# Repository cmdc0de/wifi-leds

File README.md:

# wifi-leds
wifi controlled LEDs

Goal of project:
* Build a web server on esp 32
* use a n-type mosfet to control power to an APA 102c LED strip
* use a ATECC608a for crypto and random number generator. you ask why? I say why not?
* add 2 displays 1. 2.4 SPI touch screen and 1 OLED I2C 
  * Again you ask why? mostly becuase I'm also working on the darknet 8 badge and one of these will be on that badge and it'll help me prepare.
* Pull out JTAG pins so I can try to debug from container.  Harder than it sounds becuase you need to run the open ocd server

Secondary Goals:
* Make the traces as thick as possible, so I can try to not only mill the board with my Bantam but also use 'print' the board using the Voltera.

Code:
* On linux:
* run buildESPContainer.sh
* ./runESPContainer.sh
* cd into firmware directory
* make menuconfig - set up usb port your usb to serial programmer is registered as
* make flash - build and push to dev board
* make monitor 
*

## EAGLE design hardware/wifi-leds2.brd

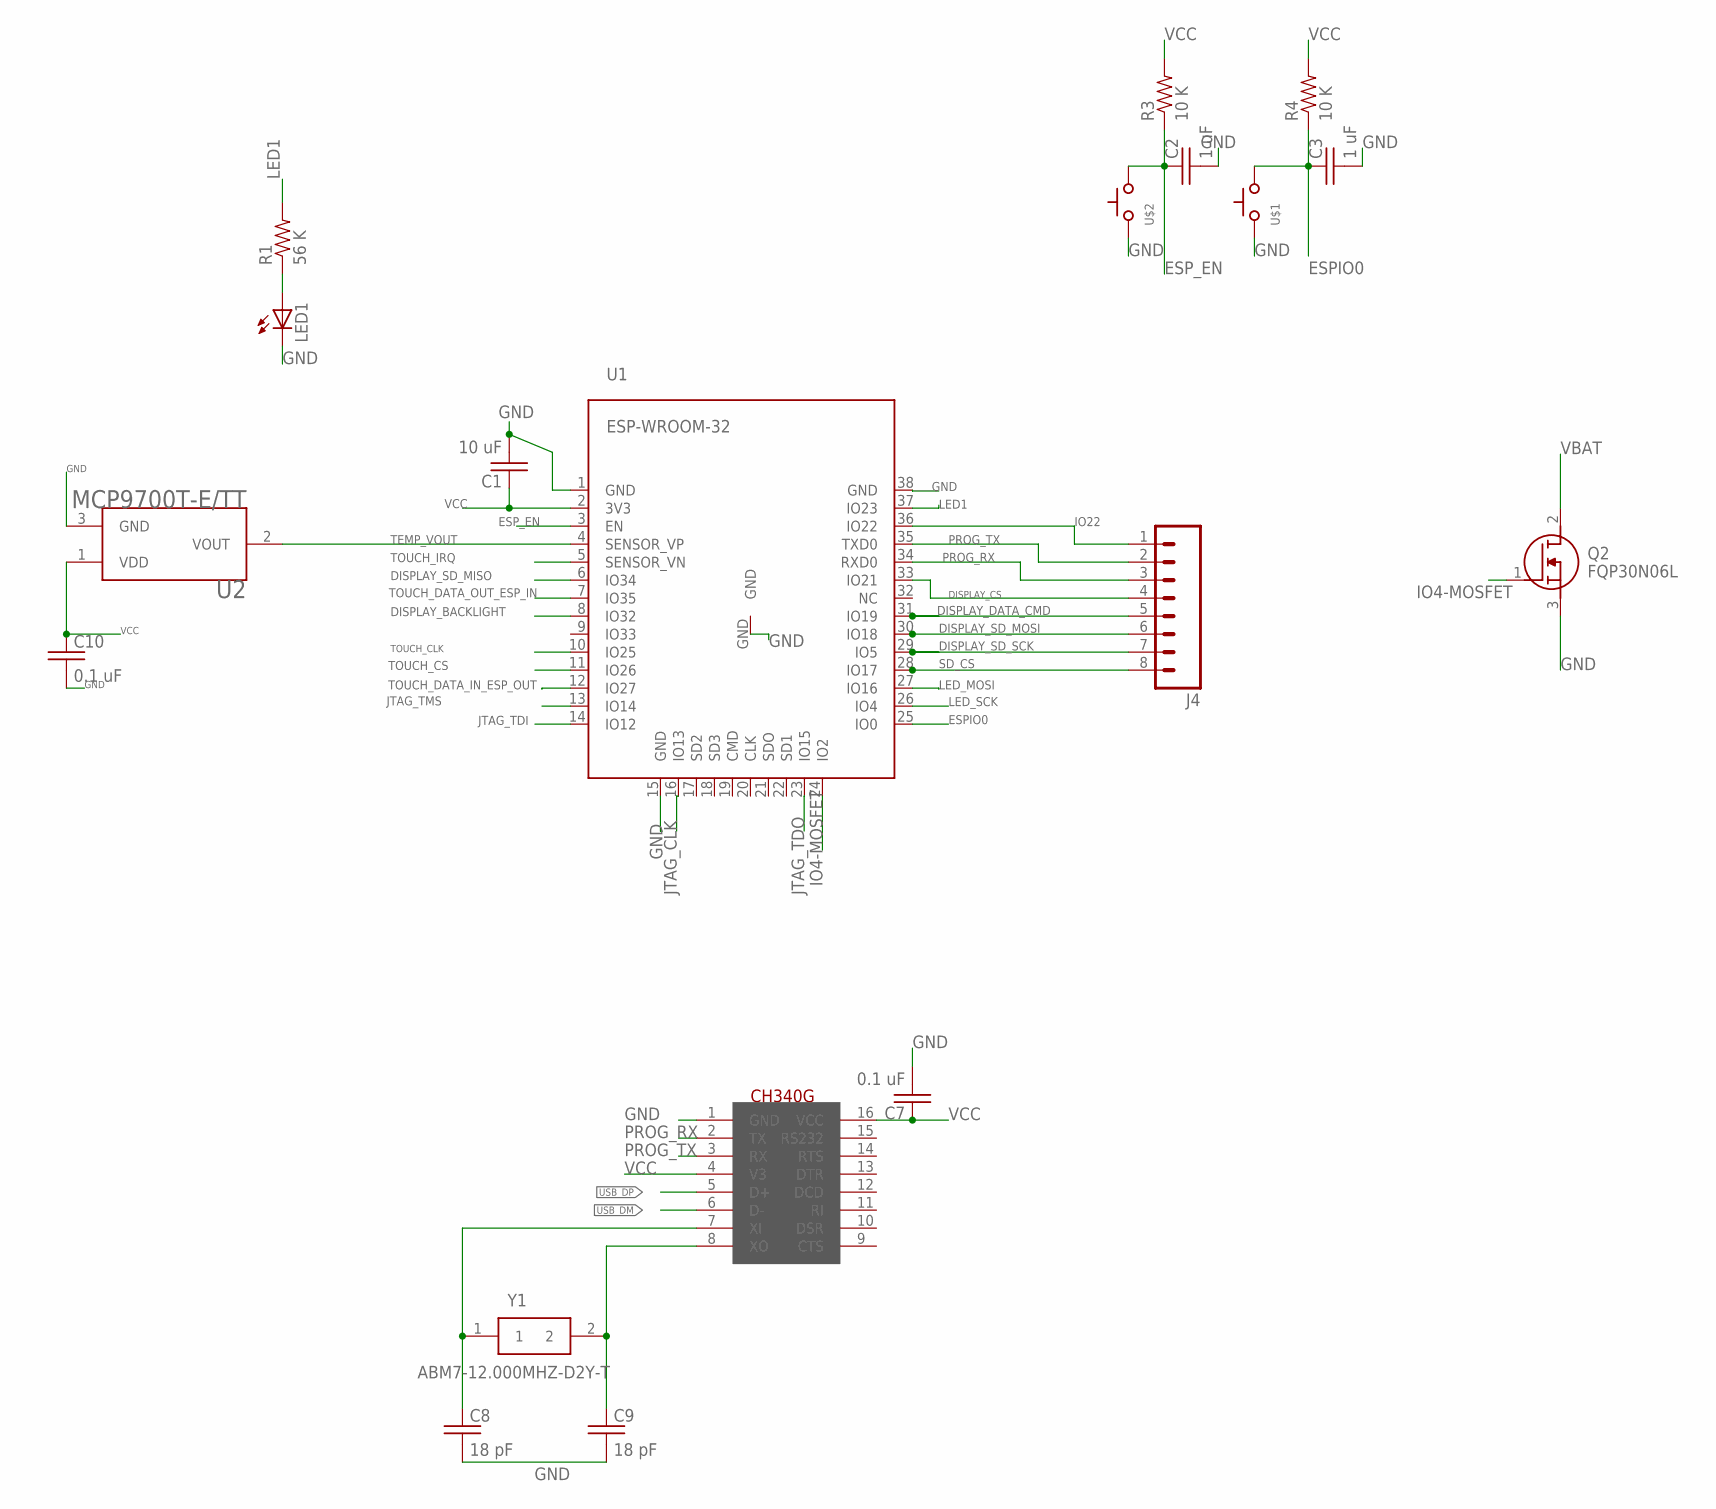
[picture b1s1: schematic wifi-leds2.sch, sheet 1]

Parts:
C1: 10 uF; C0805
C2, C3: 1 uF; C0805
C7, C10: 0.1 uF; C0805
C8, C9: 18 pF; C0805
J4: M08; 1X08_ROUND
LED1: LED3MM
Q2: FQP30N06L; TO254P470X1016X2019-3P
R1: 56 K; 0805
R3, R4: 10 K; 0805
U1: ESP-WROOM-32
U2: MCP9700T-E/TT; SOT95P237X112-3N
U$1, U$2: SWITCH_TACTILETACTILE-2PIN-NARROW; TACTILE-2PIN-NARROW
U$6: CH340G; SOIC16
Y1: ABM7-12.000MHZ-D2Y-T; ABM7

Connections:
DISPLAY_BACKLIGHT: U1.8 (IO32); also elsewhere on the board
DISPLAY_CS: J4.4, U1.33 (IO21); also elsewhere on the board
DISPLAY_DATA_CMD: J4.5, U1.31 (IO19); also elsewhere on the board
DISPLAY_SD_MISO: U1.6 (IO34); also elsewhere on the board
DISPLAY_SD_MOSI: J4.6, U1.30 (IO18); also elsewhere on the board
DISPLAY_SD_SCK: J4.7, U1.29 (IO5); also elsewhere on the board
ESPIO0: C3.1, R4.1, U1.25 (IO0), U$1.P$1 (A)
ESP_EN: C2.1, R3.1, U1.3 (EN), U$2.P$1 (A)
GND: C1.2, C2.2, C3.2, C7.2, C8.2, C9.2, C10.2, LED1.K (C), Q2.3 (S), U1.1 (GND), U1.15 (GND), U1.38 (GND), U1.GND, U2.3 (GND), U$1.P$2 (C), U$2.P$2 (C), U$6.1 (GND); also elsewhere on the board
IO4-MOSFET: Q2.1 (G), U1.24 (IO2)
IO22: J4.1, U1.36 (IO22)
JTAG_CLK: U1.16 (IO13); also elsewhere on the board
JTAG_TDI: U1.14 (IO12); also elsewhere on the board
JTAG_TDO: U1.23 (IO15); also elsewhere on the board
JTAG_TMS: U1.13 (IO14); also elsewhere on the board
LED1: R1.2, U1.37 (IO23)
LED_MOSI: U1.27 (IO16); also elsewhere on the board
LED_SCK: U1.26 (IO4); also elsewhere on the board
unnamed: LED1.A, R1.1
unnamed: C8.1, U$6.7 (XI), Y1.1
unnamed: C9.1, U$6.8 (XO), Y1.2
PROG_RX: J4.3, U1.34 (RXD0), U$6.2 (TX); also elsewhere on the board
PROG_TX: J4.2, U1.35 (TXD0), U$6.3 (RX); also elsewhere on the board
SD_CS: J4.8, U1.28 (IO17); also elsewhere on the board
TEMP_VOUT: U1.4 (SENSOR_VP), U2.2 (VOUT)
TOUCH_CLK: U1.10 (IO25); also elsewhere on the board
TOUCH_CS: U1.11 (IO26); also elsewhere on the board
TOUCH_DATA_IN_ESP_OUT: U1.12 (IO27); also elsewhere on the board
TOUCH_DATA_OUT_ESP_IN: U1.7 (IO35); also elsewhere on the board
TOUCH_IRQ: U1.5 (SENSOR_VN); also elsewhere on the board
USB_DM: U$6.6 (D-); also elsewhere on the board
USB_DP: U$6.5 (D+); also elsewhere on the board
VBAT: Q2.2 (D); also elsewhere on the board
VCC: C1.1, C7.1, C10.1, R3.2, R4.2, U1.2 (3V3), U2.1 (VDD), U$6.4 (V3), U$6.16 (VCC); also elsewhere on the board

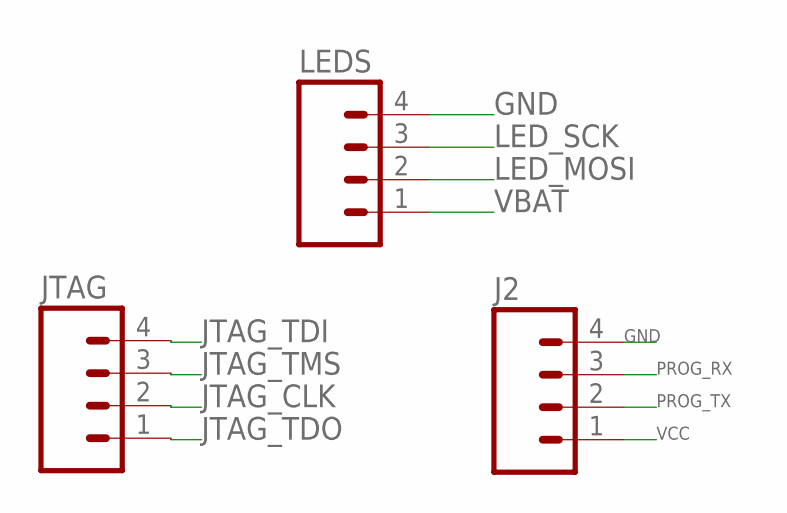
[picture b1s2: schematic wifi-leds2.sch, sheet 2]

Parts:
J2: M04PTH; 1X04
JTAG: M04PTH; 1X04
LEDS: M04POLAR; MOLEX-1X4

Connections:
GND: J2.4, LEDS.4; also elsewhere on the board
JTAG_CLK: JTAG.2; also elsewhere on the board
JTAG_TDI: JTAG.4; also elsewhere on the board
JTAG_TDO: JTAG.1; also elsewhere on the board
JTAG_TMS: JTAG.3; also elsewhere on the board
LED_MOSI: LEDS.2; also elsewhere on the board
LED_SCK: LEDS.3; also elsewhere on the board
PROG_RX: J2.3; also elsewhere on the board
PROG_TX: J2.2; also elsewhere on the board
VBAT: LEDS.1; also elsewhere on the board
VCC: J2.1; also elsewhere on the board

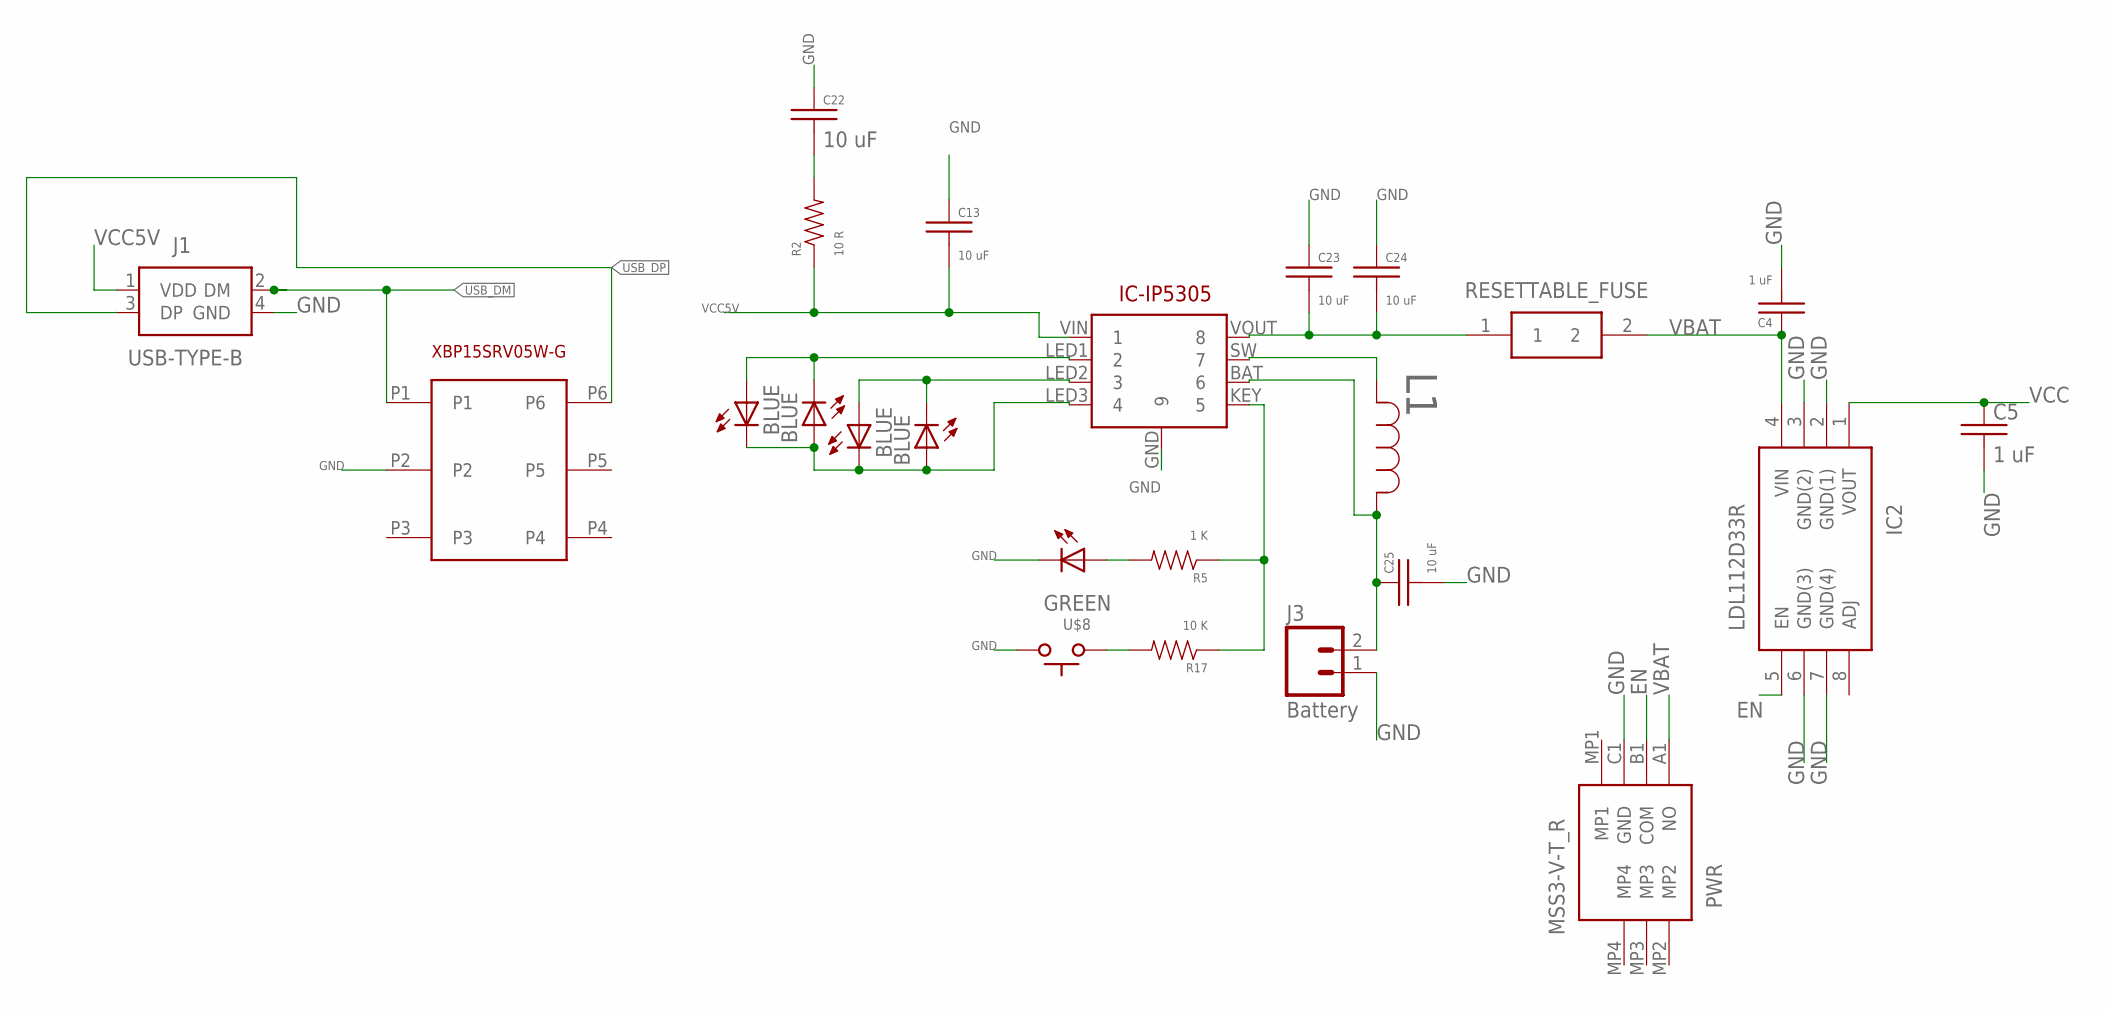
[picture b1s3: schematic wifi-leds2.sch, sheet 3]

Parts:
C4, C5: 1 uF; C0805
C13, C22, C23, C24, C25: 10 uF; C0805
CL1, CL2, CL3, CL4: BLUE; LED-1206
IC2: LDL112D33R; SOIC127P600X175-8N
IC-IP5305: IP5305ESOP8; SOIC127P600X165-8
J1: USB-TYPE-B; 61400413321
J3: Battery; JST-2-PTH
KEYLED: GREEN; LED-1206
L1: 2.2uH; IND_TAIYO_NRS4018
PWR: MSS3-V-T_R; MSS3VTR
R2: 10 R; 0805
R5: 1 K; 0805
R17: 10 K; 0805
RESETTABLE_FUSE: 0ZCJ0050FF2G; FUSC3216X55N
U$8: SWITCH_TACTILETACTILE-2PIN-NARROW; TACTILE-2PIN-NARROW
U$9: XBP15SRV05W-G; SOT-26P-XBP15SRV05W-G

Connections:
EN: IC2.5 (EN), PWR.B1 (COM)
GND: C4.2, C5.2, C13.1, C22.1, C23.1, C24.1, C25.2, IC2.2 (GND(1)), IC2.3 (GND(2)), IC2.6 (GND(3)), IC2.7 (GND(4)), IC-IP5305.GND (9), J1.4 (GND), J3.1, KEYLED.C, PWR.C1 (GND), U$8.P$1 (A), U$9.P2; also elsewhere on the board
unnamed: CL1.A, CL2.C, IC-IP5305.LED1 (2)
unnamed: CL3.A, CL4.C, IC-IP5305.LED2 (3)
unnamed: CL1.C, CL2.A, CL3.C, CL4.A, IC-IP5305.LED3 (4)
unnamed: C22.2, R2.2
unnamed: IC-IP5305.SW (7), L1.2
unnamed: C25.1, IC-IP5305.BAT (6), J3.2, L1.1
unnamed: IC-IP5305.KEY (5), R5.1, R17.1
unnamed: KEYLED.A, R5.2
unnamed: R17.2, U$8.P$2 (C)
unnamed: C23.2, C24.2, IC-IP5305.VOUT (8), RESETTABLE_FUSE.1
USB_DM: J1.2 (DM), U$9.P1; also elsewhere on the board
USB_DP: J1.3 (DP), U$9.P6; also elsewhere on the board
VBAT: C4.1, IC2.4 (VIN), PWR.A1 (NO), RESETTABLE_FUSE.2; also elsewhere on the board
VCC: C5.1, IC2.1 (VOUT); also elsewhere on the board
VCC5V: C13.2, IC-IP5305.VIN (1), J1.1 (VDD), R2.1

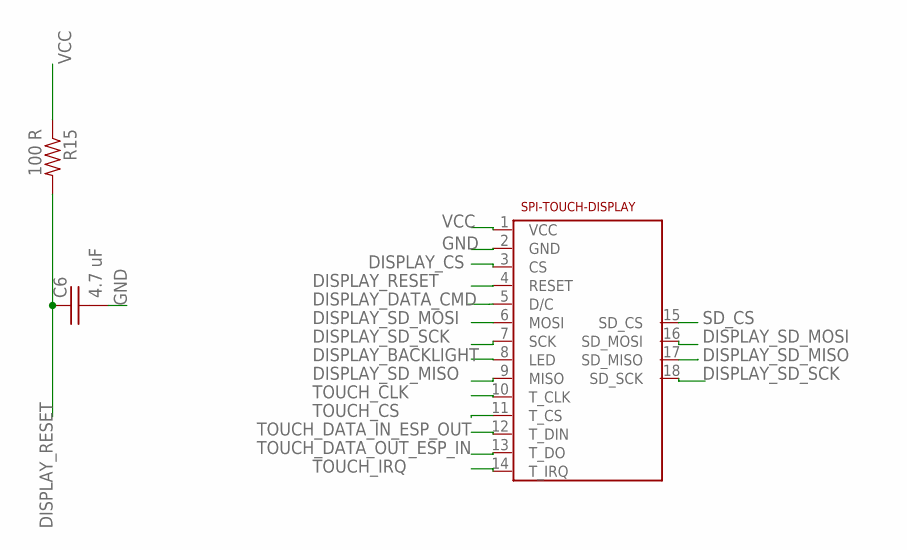
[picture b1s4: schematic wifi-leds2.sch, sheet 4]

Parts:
C6: 4.7 uF; C0805
R15: 100 R; 0805
U$3: 2.4-SPI-TFT-TOUCH-SSD-MODULE

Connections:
DISPLAY_BACKLIGHT: U$3.8 (LED); also elsewhere on the board
DISPLAY_CS: U$3.3 (CS); also elsewhere on the board
DISPLAY_DATA_CMD: U$3.5 (D/C); also elsewhere on the board
DISPLAY_RESET: C6.1, R15.2, U$3.4 (RESET)
DISPLAY_SD_MISO: U$3.9 (MISO), U$3.17 (SD_MISO); also elsewhere on the board
DISPLAY_SD_MOSI: U$3.6 (MOSI), U$3.16 (SD_MOSI); also elsewhere on the board
DISPLAY_SD_SCK: U$3.7 (SCK), U$3.18 (SD_SCK); also elsewhere on the board
GND: C6.2, U$3.2 (GND); also elsewhere on the board
SD_CS: U$3.15 (SD_CS); also elsewhere on the board
TOUCH_CLK: U$3.10 (T_CLK); also elsewhere on the board
TOUCH_CS: U$3.11 (T_CS); also elsewhere on the board
TOUCH_DATA_IN_ESP_OUT: U$3.12 (T_DIN); also elsewhere on the board
TOUCH_DATA_OUT_ESP_IN: U$3.13 (T_DO); also elsewhere on the board
TOUCH_IRQ: U$3.14 (T_IRQ); also elsewhere on the board
VCC: R15.1, U$3.1 (VCC); also elsewhere on the board

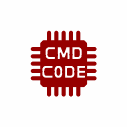
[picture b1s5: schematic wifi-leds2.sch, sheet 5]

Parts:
U$5: CMD_C0DE_LOGOCMD_CODE_LOGO_TOP_COPPER; CMD_C0DE_LOGO_TOP_COPPER

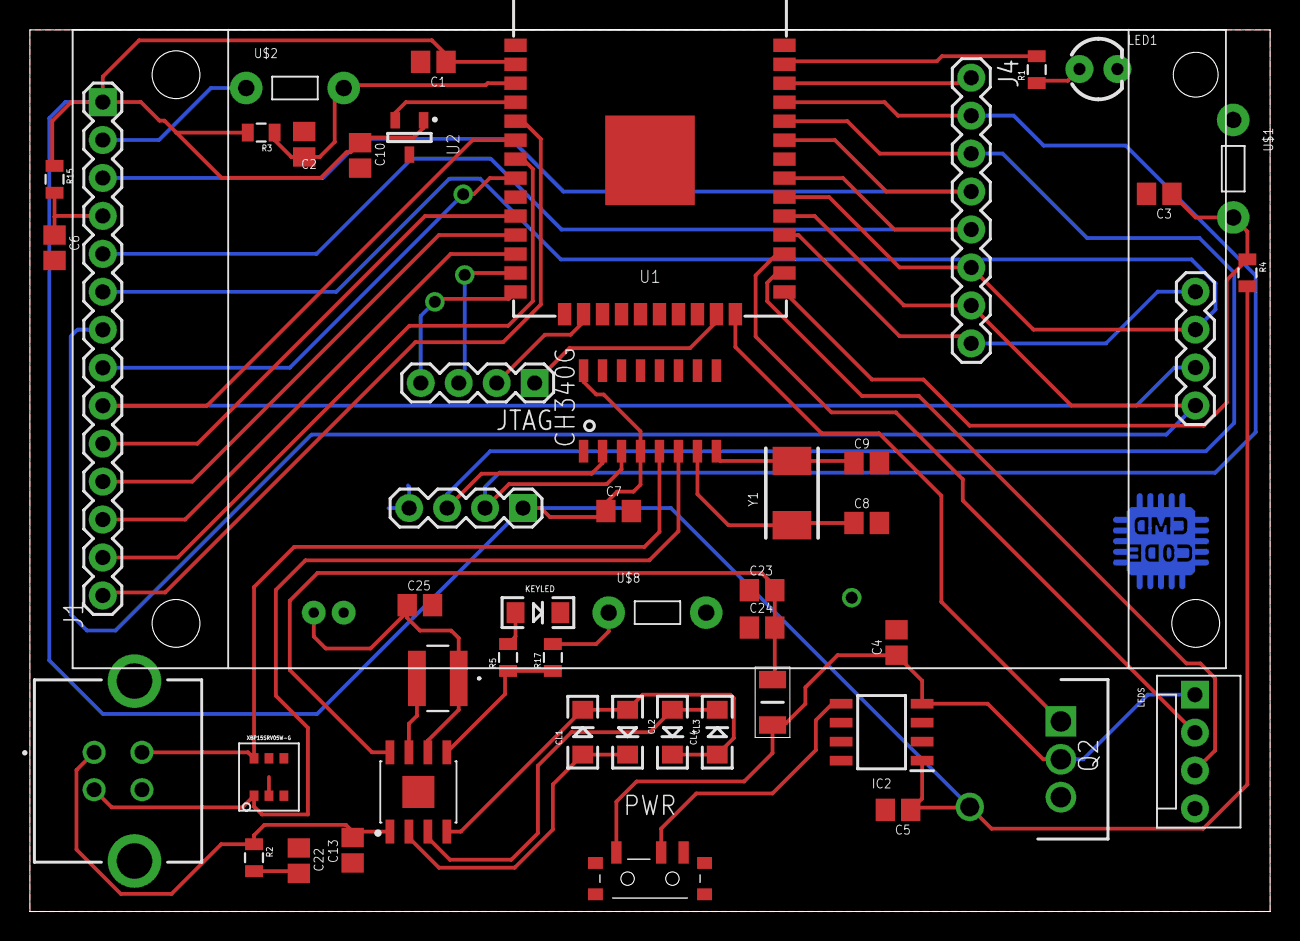
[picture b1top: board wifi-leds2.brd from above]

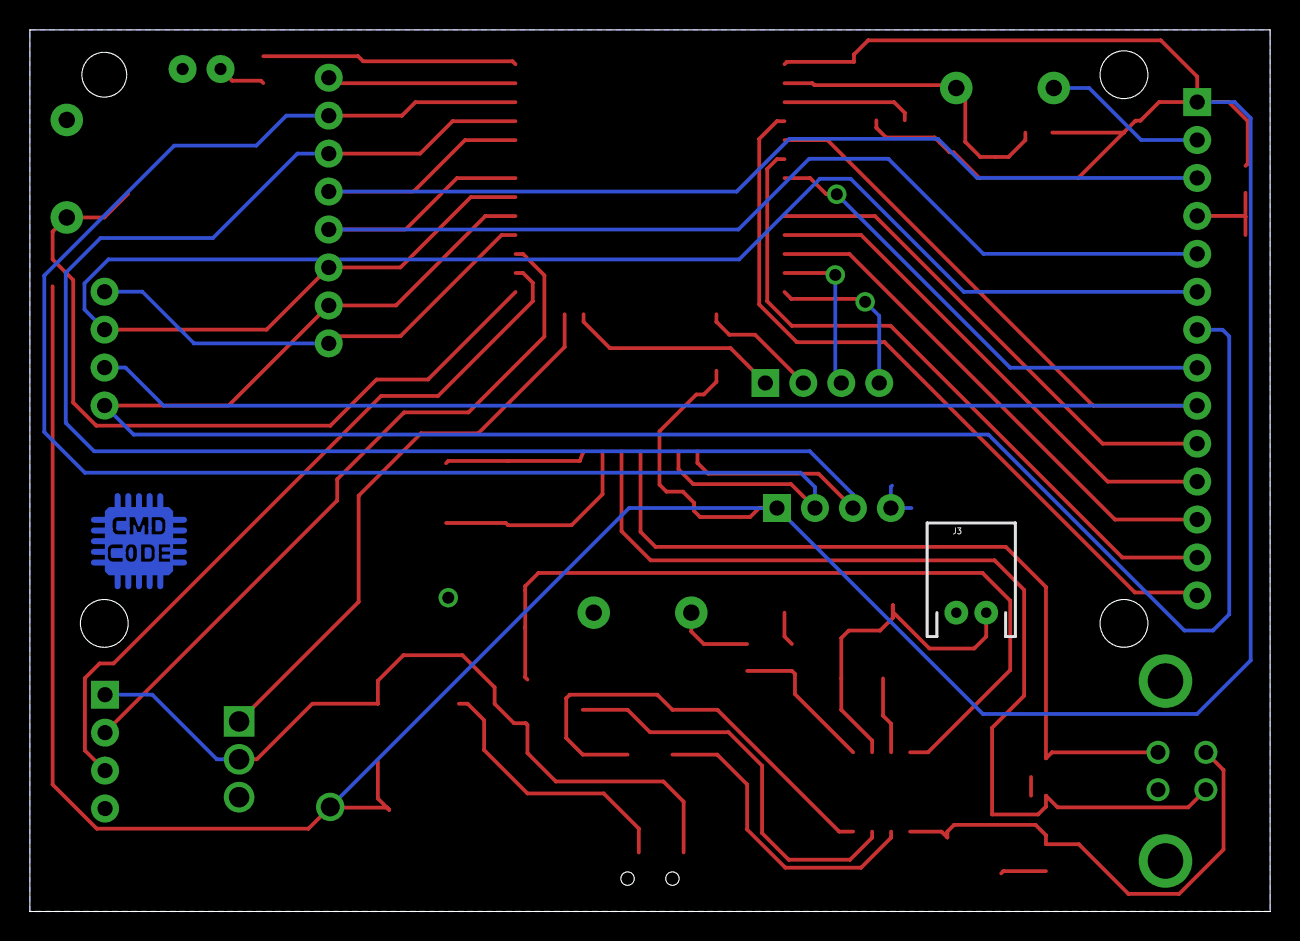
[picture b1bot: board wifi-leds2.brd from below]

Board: 2 copper layers, 83.0 x 59.0 mm, 50 parts (2 on the bottom side), 47 nets.

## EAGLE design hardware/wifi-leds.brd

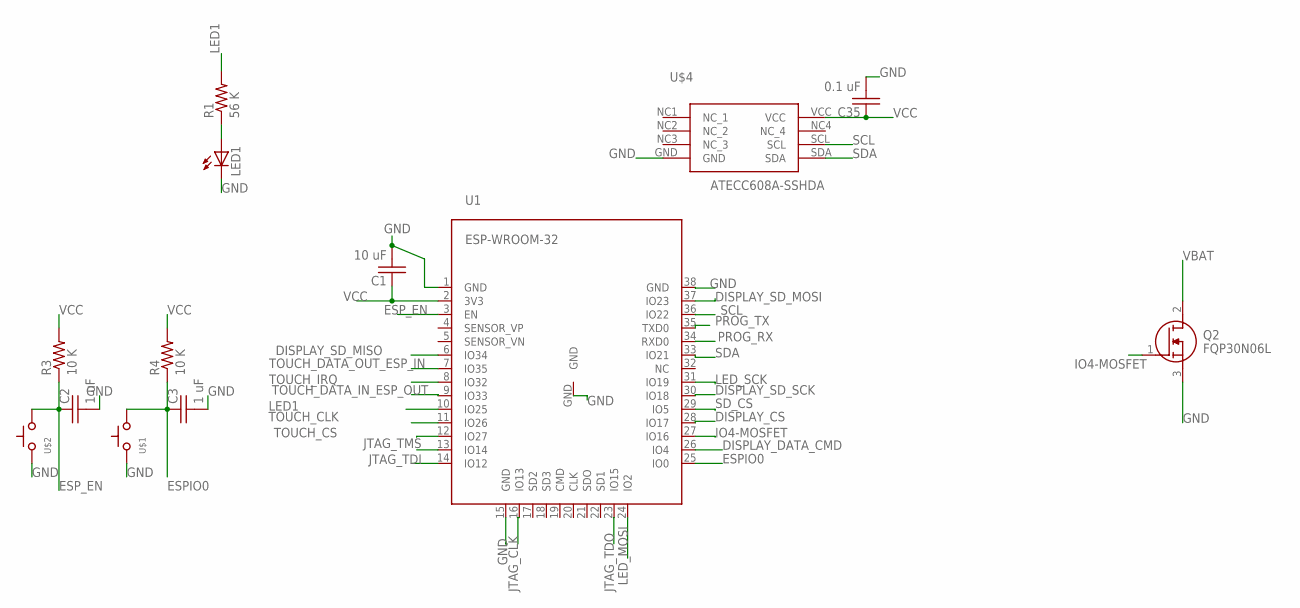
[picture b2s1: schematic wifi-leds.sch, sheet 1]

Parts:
C1: 10 uF; C0805
C2, C3: 1 uF; C0805
C35: 0.1 uF; C0805
LED1: LED3MM
Q2: FQP30N06L; TO254P470X1016X2019-3P
R1: 56 K; 0805
R3, R4: 10 K; 0805
U1: ESP-WROOM-32
U$1, U$2: SWITCH_TACTILETACTILE-2PIN-NARROW; TACTILE-2PIN-NARROW
U$4: ATECC608A-SSHDA; 8-SOIC

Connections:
DISPLAY_CS: U1.28 (IO17); also elsewhere on the board
DISPLAY_DATA_CMD: U1.26 (IO4); also elsewhere on the board
DISPLAY_SD_MISO: U1.6 (IO34); also elsewhere on the board
DISPLAY_SD_MOSI: U1.37 (IO23); also elsewhere on the board
DISPLAY_SD_SCK: U1.30 (IO18); also elsewhere on the board
ESPIO0: C3.1, R4.1, U1.25 (IO0), U$1.P$1 (A)
ESP_EN: C2.1, R3.1, U1.3 (EN), U$2.P$1 (A)
GND: C1.2, C2.2, C3.2, C35.2, LED1.K (C), Q2.3 (S), U1.1 (GND), U1.15 (GND), U1.38 (GND), U1.GND, U$1.P$2 (C), U$2.P$2 (C), U$4.GND; also elsewhere on the board
IO4-MOSFET: Q2.1 (G), U1.27 (IO16)
JTAG_CLK: U1.16 (IO13); also elsewhere on the board
JTAG_TDI: U1.14 (IO12); also elsewhere on the board
JTAG_TDO: U1.23 (IO15); also elsewhere on the board
JTAG_TMS: U1.13 (IO14); also elsewhere on the board
LED1: R1.2, U1.10 (IO25)
LED_MOSI: U1.24 (IO2); also elsewhere on the board
LED_SCK: U1.31 (IO19); also elsewhere on the board
unnamed: LED1.A, R1.1
PROG_RX: U1.34 (RXD0); also elsewhere on the board
PROG_TX: U1.35 (TXD0); also elsewhere on the board
SCL: U1.36 (IO22), U$4.SCL; also elsewhere on the board
SDA: U1.33 (IO21), U$4.SDA; also elsewhere on the board
SD_CS: U1.29 (IO5); also elsewhere on the board
TOUCH_CLK: U1.11 (IO26); also elsewhere on the board
TOUCH_CS: U1.12 (IO27); also elsewhere on the board
TOUCH_DATA_IN_ESP_OUT: U1.9 (IO33); also elsewhere on the board
TOUCH_DATA_OUT_ESP_IN: U1.7 (IO35); also elsewhere on the board
TOUCH_IRQ: U1.8 (IO32); also elsewhere on the board
VBAT: Q2.2 (D); also elsewhere on the board
VCC: C1.1, C35.1, R3.2, R4.2, U1.2 (3V3), U$4.VCC; also elsewhere on the board

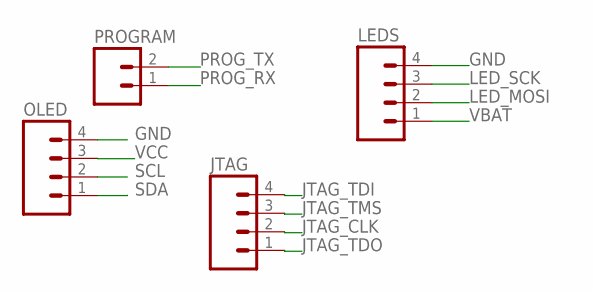
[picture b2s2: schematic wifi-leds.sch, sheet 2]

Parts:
JTAG: M04PTH; 1X04
LEDS: M04POLAR; MOLEX-1X4
OLED: M04PTH; 1X04
PROGRAM: M02PTH; 1X02

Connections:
GND: LEDS.4, OLED.4; also elsewhere on the board
JTAG_CLK: JTAG.2; also elsewhere on the board
JTAG_TDI: JTAG.4; also elsewhere on the board
JTAG_TDO: JTAG.1; also elsewhere on the board
JTAG_TMS: JTAG.3; also elsewhere on the board
LED_MOSI: LEDS.2; also elsewhere on the board
LED_SCK: LEDS.3; also elsewhere on the board
PROG_RX: PROGRAM.1; also elsewhere on the board
PROG_TX: PROGRAM.2; also elsewhere on the board
SCL: OLED.2; also elsewhere on the board
SDA: OLED.1; also elsewhere on the board
VBAT: LEDS.1; also elsewhere on the board
VCC: OLED.3; also elsewhere on the board

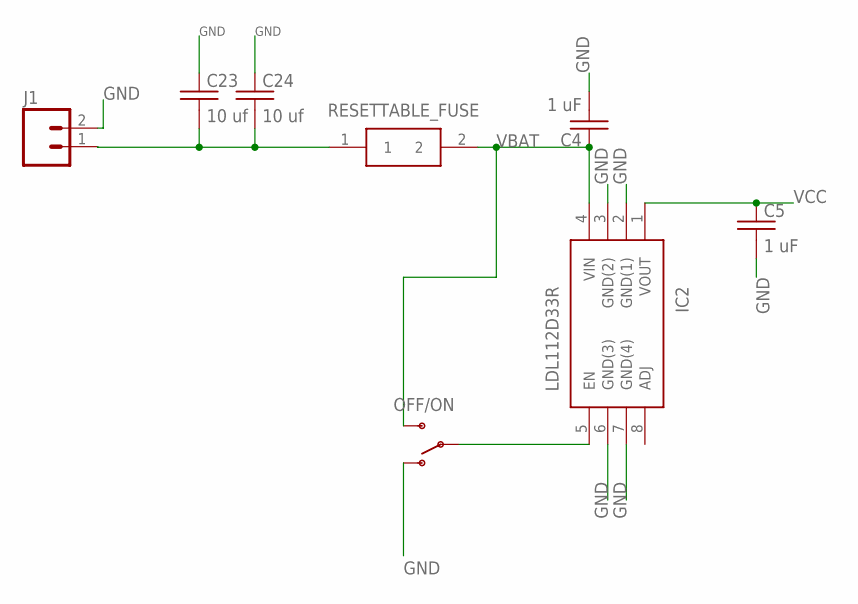
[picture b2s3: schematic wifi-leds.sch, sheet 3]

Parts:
C4, C5: 1 uF; C0805
C23, C24: 10 uf; C0805
IC2: LDL112D33R; SOIC127P600X175-8N
J1: M02PTH; 1X02
OFF/ON: SWITCH-SPSTKIT; SWITCH-SPDT_KIT
RESETTABLE_FUSE: 0ZCJ0050FF2G; FUSC3216X55N

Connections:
GND: C4.2, C5.2, C23.1, C24.1, IC2.2 (GND(1)), IC2.3 (GND(2)), IC2.6 (GND(3)), IC2.7 (GND(4)), J1.2, OFF/ON.1 (O); also elsewhere on the board
unnamed: IC2.5 (EN), OFF/ON.2
unnamed: C23.2, C24.2, J1.1, RESETTABLE_FUSE.1
VBAT: C4.1, IC2.4 (VIN), OFF/ON.3 (S), RESETTABLE_FUSE.2; also elsewhere on the board
VCC: C5.1, IC2.1 (VOUT); also elsewhere on the board

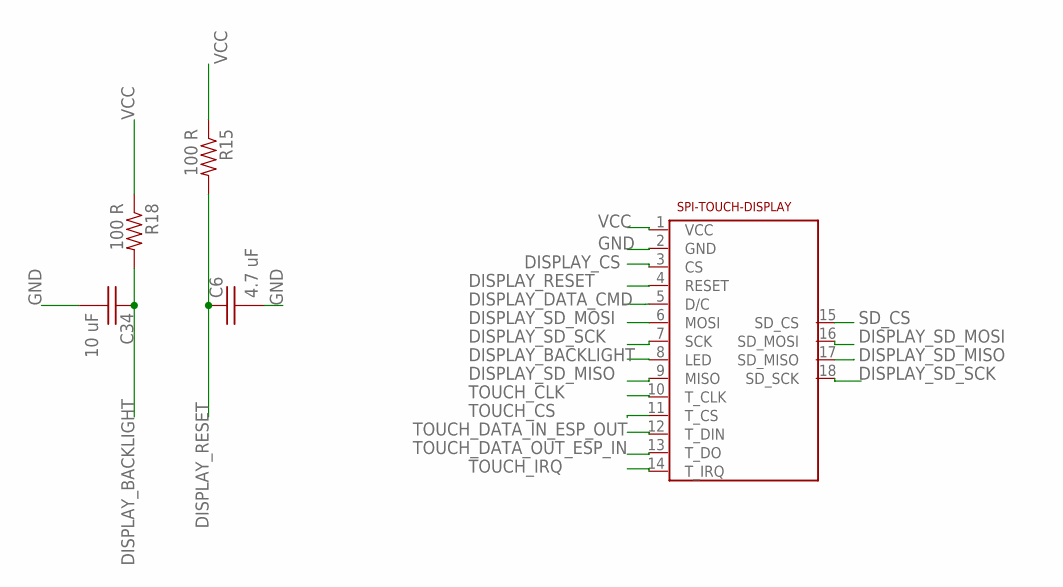
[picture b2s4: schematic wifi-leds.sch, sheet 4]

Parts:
C6: 4.7 uF; C0805
C34: 10 uF; C0805
R15, R18: 100 R; 0805
U$3: 2.4-SPI-TFT-TOUCH-SSD-MODULE

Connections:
DISPLAY_BACKLIGHT: C34.1, R18.2, U$3.8 (LED)
DISPLAY_CS: U$3.3 (CS); also elsewhere on the board
DISPLAY_DATA_CMD: U$3.5 (D/C); also elsewhere on the board
DISPLAY_RESET: C6.1, R15.2, U$3.4 (RESET)
DISPLAY_SD_MISO: U$3.9 (MISO), U$3.17 (SD_MISO); also elsewhere on the board
DISPLAY_SD_MOSI: U$3.6 (MOSI), U$3.16 (SD_MOSI); also elsewhere on the board
DISPLAY_SD_SCK: U$3.7 (SCK), U$3.18 (SD_SCK); also elsewhere on the board
GND: C6.2, C34.2, U$3.2 (GND); also elsewhere on the board
SD_CS: U$3.15 (SD_CS); also elsewhere on the board
TOUCH_CLK: U$3.10 (T_CLK); also elsewhere on the board
TOUCH_CS: U$3.11 (T_CS); also elsewhere on the board
TOUCH_DATA_IN_ESP_OUT: U$3.12 (T_DIN); also elsewhere on the board
TOUCH_DATA_OUT_ESP_IN: U$3.13 (T_DO); also elsewhere on the board
TOUCH_IRQ: U$3.14 (T_IRQ); also elsewhere on the board
VCC: R15.1, R18.1, U$3.1 (VCC); also elsewhere on the board

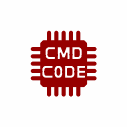
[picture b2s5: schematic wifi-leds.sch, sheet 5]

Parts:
U$5: CMD_C0DE_LOGOCMD_CODE_LOGO_TOP_COPPER; CMD_C0DE_LOGO_TOP_COPPER

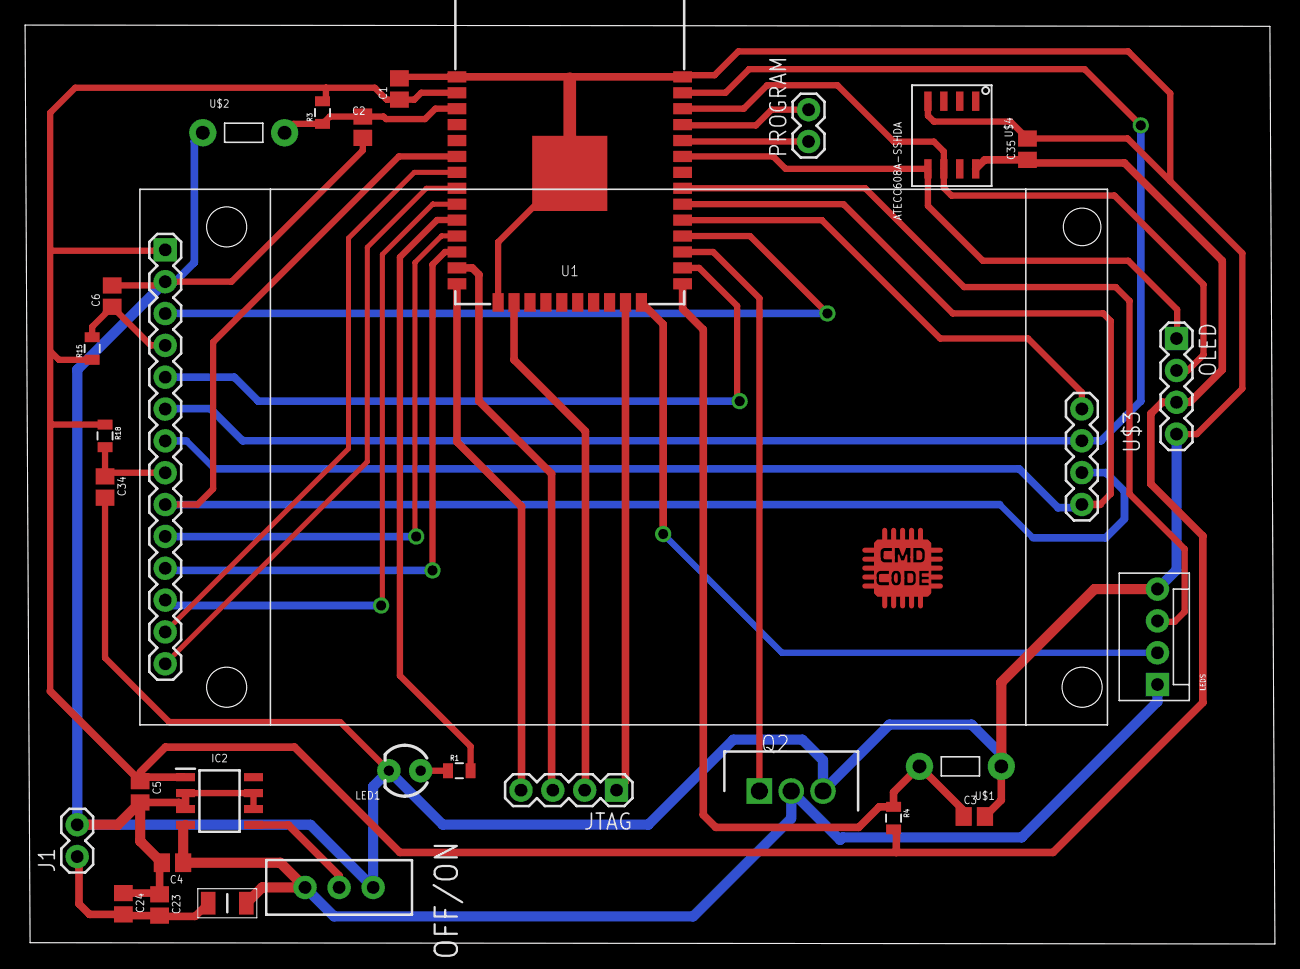
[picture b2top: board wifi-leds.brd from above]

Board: 2 copper layers, 99.7 x 73.3 mm, 31 parts (0 on the bottom side), 33 nets.

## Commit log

2019-02-12 setting up initial project for wifi leds
2019-02-21 basic compile
2019-02-27 working leds
2019-02-27 cleaned up code added vimrc to container
2019-03-23 adding hardware files
2019-03-23 Update README.md
    basic goals and instructions
2019-03-23 updated ignore, minor trace moves
2019-03-23 added logo
2019-03-30 shrunk foot print to fit on to a smaller fr4 board I have
2019-09-02 redesign of the wifi LED board
2019-10-19 updated gnd
